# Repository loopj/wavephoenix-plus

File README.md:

# WavePhoenix+

> [!IMPORTANT]  
> This is beta hardware! You'll need a copy of the WavePhoenix+ firmware from loopj to use this board, which is not yet publicly available.

The WavePhoenix+ is a custom PCB which allows you to add WaveBird support to portable Wii/GameCube consoles. It is footprint compatible with the 4Layer Technologies [GC+ 2.0](https://4layertech.com/products/gc-2) board, and emulates both a physical GameCube controller, as well as a WaveBird receiver.

## Features

- Footprint compatible with [GC+ 2](https://4layertech.com/products/gc-2)
- Captures digital/analog inputs from connected buttons, sticks, and triggers
- Captures wireless inputs from a WaveBird controller
- Support for both ERM and LRA rumble motors
- Pad to enable/disable wireless support, eg. to enable wireless only when docked
- Optional external antenna support
- Firmware updatable via Bluetooth

## Flashing Firmware

Both the WavePhoenix bootloader, and WavePhoenix+ firmware will need to be flashed to the board before it can be used. The back of the board has a set of 0.1" (2.54mm) pitch pads for flashing the bootloader via SWD.

I use a [handheld pogo flashing adapter](https://www.aliexpress.us/item/3256805545980544.html) for this, but you can also temporarily hand solder wires to the pads if you don't want to buy an adapter.

See the [WavePhoenix flashing docs](https://github.com/loopj/wavephoenix/tree/main/hardware/mini-receiver#initial-firmware-flashing) for more information on flashing the bootloader.

## Pairing Controllers

Pairing controllers can be done by entering "pairing" mode. You can enter pairing mode by briefly bridging the `BTN` pads on the board, typically using a tact switch. Alternatively you can enter pairing mode from the WavePhoenix+ homebrew.

## Updating Firmware

Once the WavePhoenix+ firmware is initially flashed, it can only be flashed again once bootloader mode is entered. To enter bootloader mode, bridge the `BTN` pads on the board for more than 3 seconds. Alternatively, you can enter bootloader mode from the WavePhoenix+ homebrew.

## External Antenna

It can often be desirable to use an external antenna on builds.

To use an external antenna, you'll need to carefully remove the onboard chip antenna from the RF-BM-BG22C3 with hot air station or soldering iron. You'll then need to add a 0Ω resistor to bridge the antenna trace to the external antenna connector.

I'd recommend covering the nearby components with Kapton tape before attempting to remove the chip antenna with hot air.

You'll need to use a a 2.4GHz antenna with an IPEX MHF 4 (or compatible) connector.

## Rumble Motors

The board uses a DRV2603 haptic driver for rumble support, which supports both ERM and LRA rumble motors. The board is configured to use an ERM motor by default, but you can change this by bridging the `LRA` pad on the board.

## Enabling/Disabling Wireless

Wireless is disabled by default to allow for a lower power mode when in portable mode. To enable wireless, connect the top half of the `WEN` pads to `GND`.

For example, you may want to use either a physical switch or a GPIO to control the `WEN` pads, so that you can enable wireless when docked, and disable it when undocked.

The radio SoC uses very little power compared to a powered Wii/GameCube/N64 so it is often more convenient to just enable wireless permanently when the board is powered. To do this, simply bridge the `WEN` pad on the board.

## Connecting Buttons and Sticks

The pinout of the board is identical to the 4Layer Technologies GC+ 2.0 board.

## Limitations

This is a very specialist project, designed for use in portable Wii/GameCube/N64 consoles where having support for a wireless controller is desirable, such as "dockable" portables.

If you are building a portable where that is not a requirement, then you should buy a [GC+ 2.0](https://4layertech.com/products/gc-2) board from the fine folks at 4Layer Technologies instead.

The firmware currently does not support features such as dead zone configuration, setting stick limits, or other advanced controller options.

I will likely add support for configuring basic stick limits, and inverting stick axes via either the WavePhoenix+ homebrew, or a web browser Bluetooth UI in future.

## License

The firmware in this repository is licensed under the [MIT License](firmware/LICENSE).

The hardware is licensed under the [Solderpad Hardware License v2.1](hardware/LICENSE).

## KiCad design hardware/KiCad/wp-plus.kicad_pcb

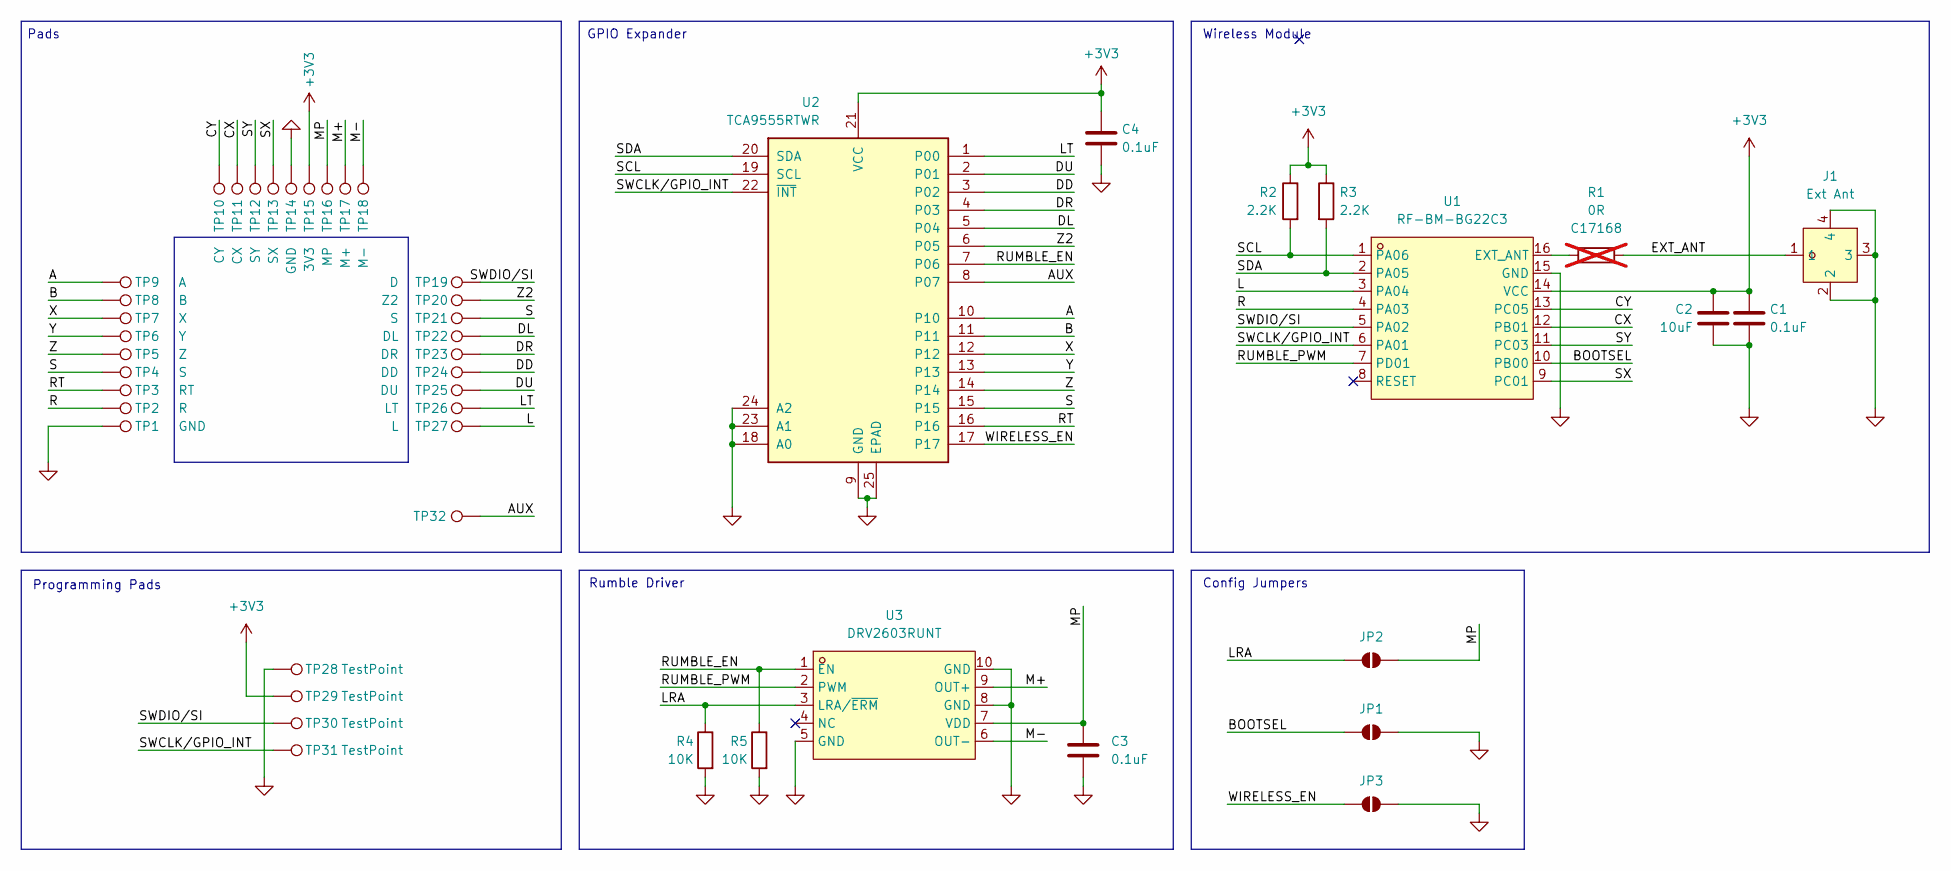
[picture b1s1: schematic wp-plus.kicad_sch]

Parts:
C1, C3, C4: 0.1uF; C_0402_1005Metric; LCSC C1525
C2: 10uF; C_0402_1005Metric; LCSC C15525
J1: Ext Ant; IPEX-SMD_4P-L1.7-W1.7-LS2.0-L-4; LCSC C7429355
JP1, JP2, JP3: SolderJumper_2_Open; SolderJumper-Small
R1: 0R; R_0402_DNP; LCSC C17168; not fitted
R2, R3: 2.2K; R_0402_1005Metric; LCSC C25879
R4, R5: 10K; R_0402_1005Metric; LCSC C25744
TP1, TP14: GND; 2x1mm Castellated Pad
TP2: R; 2x1mm Castellated Pad
TP3: RT; 2x1mm Castellated Pad
TP4, TP21: S; 2x1mm Castellated Pad
TP5: Z; 2x1mm Castellated Pad
TP6: Y; 2x1mm Castellated Pad
TP7: X; 2x1mm Castellated Pad
TP8: B; 2x1mm Castellated Pad
TP9: A; 2x1mm Castellated Pad
TP10: CY; 2x1mm Castellated Pad
TP11: CX; 2x1mm Castellated Pad
TP12: SY; 2x1mm Castellated Pad
TP13: SX; 2x1mm Castellated Pad
TP15: 3V3; 2x1mm Castellated Pad
TP16: MP; 2x1mm Castellated Pad
TP17: M+; 2x1mm Castellated Pad
TP18: M-; 2x1mm Castellated Pad
TP19: D; 2x1mm Castellated Pad
TP20: Z2; 2x1mm Castellated Pad
TP22: DL; 2x1mm Castellated Pad
TP23: DR; 2x1mm Castellated Pad
TP24: DD; 2x1mm Castellated Pad
TP25: DU; 2x1mm Castellated Pad
TP26: LT; 2x1mm Castellated Pad
TP27: L; 2x1mm Castellated Pad
TP28, TP29, TP30, TP31, TP32: TestPoint; TestPoint_Pad_D1.0mm
U1: RF-BM-BG22C3; LCSC C5369196
U2: TCA9555RTWR; WQFN-24-1EP_4x4mm_P0.5mm_EP2.45x2.45mm; LCSC C140277
U3: DRV2603RUNT; QFN-10_L2.0-W2.0-P0.50-TL; LCSC C2150691

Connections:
+3V3: C1.1, C2.1, C4.1, R2.1, R3.1, TP15.1, TP29.1, U1.14 (VCC), U2.21 (VCC)
/A: TP9.1, U2.10
/AUX: TP32.1, U2.8 (P07)
/B: TP8.1, U2.11
/BOOTSEL: JP1.1 (A), U1.10 (PB00)
/CX: TP11.1, U1.12 (PB01)
/CY: TP10.1, U1.13 (PC05)
/DD: TP24.1, U2.3 (P02)
/DL: TP22.1, U2.5 (P04)
/DR: TP23.1, U2.4 (P03)
/DU: TP25.1, U2.2 (P01)
/EXT_ANT: J1.1, R1.2
/L: TP27.1, U1.3 (PA04)
/LRA: JP2.1 (A), R4.1, U3.3 (LRA/~ERM)
/LT: TP26.1, U2.1 (P00)
/M+: TP17.1, U3.9 (OUT+)
/M-: TP18.1, U3.6 (OUT-)
/MP: C3.1, JP2.2 (B), TP16.1, U3.7 (VDD)
/R: TP2.1, U1.4 (PA03)
/RT: TP3.1, U2.16
/RUMBLE_EN: R5.1, U2.7 (P06), U3.1 (EN)
/RUMBLE_PWM: U1.7 (PD01), U3.2 (PWM)
/S: TP4.1, TP21.1, U2.15
/SCL: R2.2, U1.1 (PA06), U2.19 (SCL)
/SDA: R3.2, U1.2 (PA05), U2.20 (SDA)
/SWCLK/GPIO_INT: TP31.1, U1.6 (PA01), U2.22 (~INT)
/SWDIO/SI: TP19.1, TP30.1, U1.5 (PA02)
/SX: TP13.1, U1.9 (PC01)
/SY: TP12.1, U1.11 (PC03)
/WIRELESS_EN: JP3.1 (A), U2.17
/X: TP7.1, U2.12
/Y: TP6.1, U2.13
/Z: TP5.1, U2.14
/Z2: TP20.1, U2.6 (P05)
GND: C1.2, C2.2, C3.2, C4.2, J1.2, J1.3, J1.4, JP1.2 (B), JP3.2 (B), R4.2, R5.2, TP1.1, TP14.1, TP28.1, U1.15 (GND), U2.9 (GND), U2.18 (A0), U2.23 (A1), U2.24 (A2), U2.25 (EPAD), U3.5 (GND), U3.8 (GND), U3.10 (GND)
unnamed: R1.1, U1.16 (EXT_ANT)

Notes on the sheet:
Config Jumpers
Rumble Driver
GPIO Expander
Pads
Programming Pads
Wireless Module

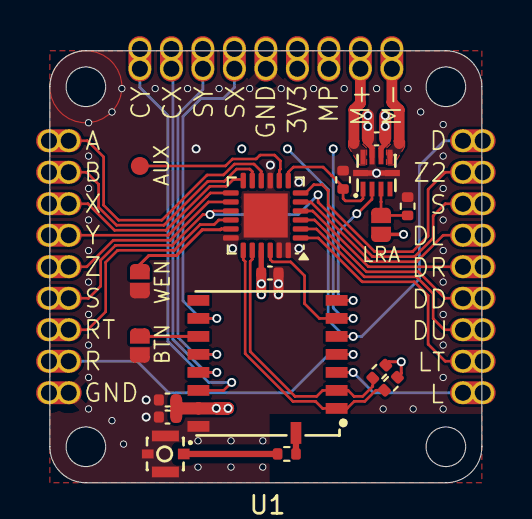
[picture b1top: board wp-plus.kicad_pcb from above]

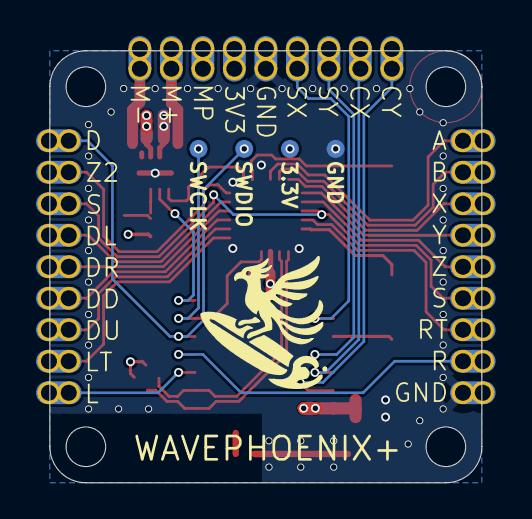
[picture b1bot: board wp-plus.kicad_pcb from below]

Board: 4 copper layers, 24.0 x 24.0 mm, 48 parts (4 on the bottom side), 36 nets.

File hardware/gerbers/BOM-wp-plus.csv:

Comment,Designator,Footprint,LCSC
TCA9555RTWR,U2,WQFN-24-1EP_4x4mm_P0.5mm_EP2.45x2.45mm,C140277
0.1uF,"C1,C3,C4",C_0402_1005Metric,C1525
10uF,C2,C_0402_1005Metric,C15525
0R,,R_0402_DNP,C17168
DRV2603RUNT,U3,QFN-10_L2.0-W2.0-P0.50-TL,C2150691
10K,"R4,R5",R_0402_1005Metric,C25744
2.2K,"R2,R3",R_0402_1005Metric,C25879
RF-BM-BG22C3,U1,RF-BM-BG22C3,C5369196
Ext Ant,J1,IPEX-SMD_4P-L1.7-W1.7-LS2.0-L-4,C7429355

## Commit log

2025-07-21 Initial public hardware release
